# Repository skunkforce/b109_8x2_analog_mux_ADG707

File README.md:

# edgy_board number b109
This design is part of the [edgy board project](https://github.com/skunkforce/edgy_boards). It provides the functionality of chip ADG707 an 8x2 analog mux. 

# getting started
This repository uses submodules. After cloning use the command 

```$ git submodule update --init --recursive```

to pull the submodules before opening the project with kicad. 

# Tests
Tests can be found in [TESTS.md](TESTS.md)

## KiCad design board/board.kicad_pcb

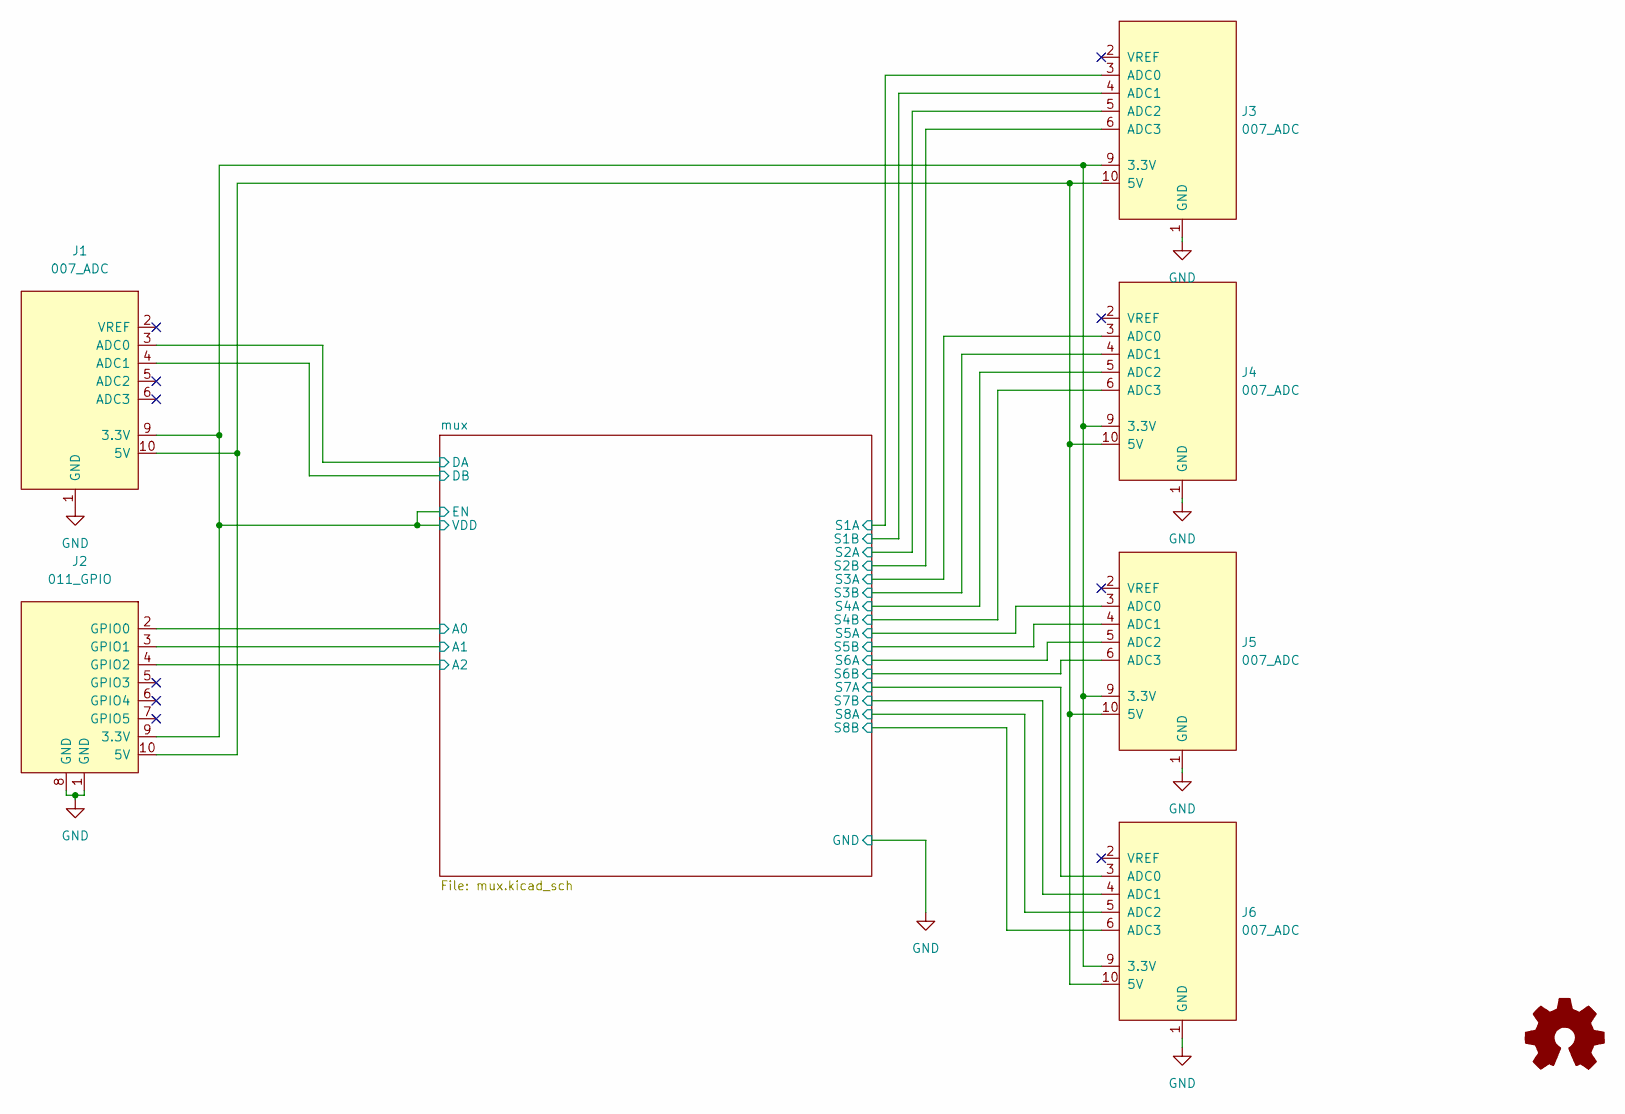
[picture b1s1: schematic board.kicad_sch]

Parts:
J1: 007_ADC; on_edge_2x05_device; lcsc C14663
J2: 011_GPIO; on_edge_2x05_device
J3, J4, J5, J6: 007_ADC; on_edge_2x05_host
LOGO1: Logo_Open_Hardware_Small; OSHW-Symbol_6.7x6mm_SilkScreen

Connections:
/mux/A0: J2.2 (GPIO0); also elsewhere on the board
/mux/A1: J2.3 (GPIO1); also elsewhere on the board
/mux/A2: J2.4 (GPIO2); also elsewhere on the board
/mux/DA: J1.3 (ADC0); also elsewhere on the board
/mux/DB: J1.4 (ADC1); also elsewhere on the board
/mux/EN: J1.9 (3.3V), J2.9 (3.3V), J3.9 (3.3V), J4.9 (3.3V), J5.9 (3.3V), J6.9 (3.3V); also elsewhere on the board
/mux/S1A: J3.3 (ADC0); also elsewhere on the board
/mux/S1B: J3.4 (ADC1); also elsewhere on the board
/mux/S2A: J3.5 (ADC2); also elsewhere on the board
/mux/S2B: J3.6 (ADC3); also elsewhere on the board
/mux/S3A: J4.3 (ADC0); also elsewhere on the board
/mux/S3B: J4.4 (ADC1); also elsewhere on the board
/mux/S4A: J4.5 (ADC2); also elsewhere on the board
/mux/S4B: J4.6 (ADC3); also elsewhere on the board
/mux/S5A: J5.3 (ADC0); also elsewhere on the board
/mux/S5B: J5.4 (ADC1); also elsewhere on the board
/mux/S6A: J5.5 (ADC2); also elsewhere on the board
/mux/S6B: J5.6 (ADC3); also elsewhere on the board
/mux/S7A: J6.3 (ADC0); also elsewhere on the board
/mux/S7B: J6.4 (ADC1); also elsewhere on the board
/mux/S8A: J6.5 (ADC2); also elsewhere on the board
/mux/S8B: J6.6 (ADC3); also elsewhere on the board
GND: J1.1 (GND), J2.1 (GND), J2.8 (GND), J3.1 (GND), J4.1 (GND), J5.1 (GND), J6.1 (GND); also elsewhere on the board
unnamed: J1.10 (5V), J2.10 (5V), J3.10 (5V), J4.10 (5V), J5.10 (5V), J6.10 (5V)

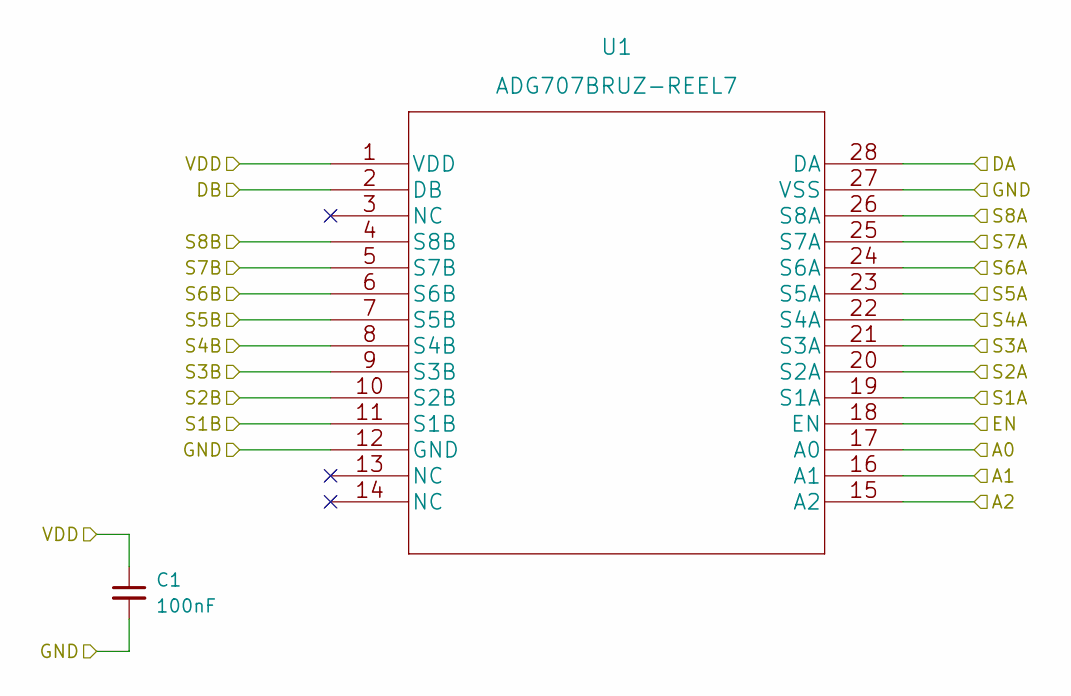
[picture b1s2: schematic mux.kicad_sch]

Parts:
C1: 100nF; C_0603_1608Metric
U1: ADG707BRUZ-REEL7; lcsc C246080

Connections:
/mux/A0: U1.17 (A0); also elsewhere on the board
/mux/A1: U1.16 (A1); also elsewhere on the board
/mux/A2: U1.15 (A2); also elsewhere on the board
/mux/DA: U1.28 (DA); also elsewhere on the board
/mux/DB: U1.2 (DB); also elsewhere on the board
/mux/EN: C1.1, U1.1 (VDD), U1.18 (EN); also elsewhere on the board
/mux/S1A: U1.19 (S1A); also elsewhere on the board
/mux/S1B: U1.11 (S1B); also elsewhere on the board
/mux/S2A: U1.20 (S2A); also elsewhere on the board
/mux/S2B: U1.10 (S2B); also elsewhere on the board
/mux/S3A: U1.21 (S3A); also elsewhere on the board
/mux/S3B: U1.9 (S3B); also elsewhere on the board
/mux/S4A: U1.22 (S4A); also elsewhere on the board
/mux/S4B: U1.8 (S4B); also elsewhere on the board
/mux/S5A: U1.23 (S5A); also elsewhere on the board
/mux/S5B: U1.7 (S5B); also elsewhere on the board
/mux/S6A: U1.24 (S6A); also elsewhere on the board
/mux/S6B: U1.6 (S6B); also elsewhere on the board
/mux/S7A: U1.25 (S7A); also elsewhere on the board
/mux/S7B: U1.5 (S7B); also elsewhere on the board
/mux/S8A: U1.26 (S8A); also elsewhere on the board
/mux/S8B: U1.4 (S8B); also elsewhere on the board
GND: C1.2, U1.12 (GND), U1.27 (VSS); also elsewhere on the board

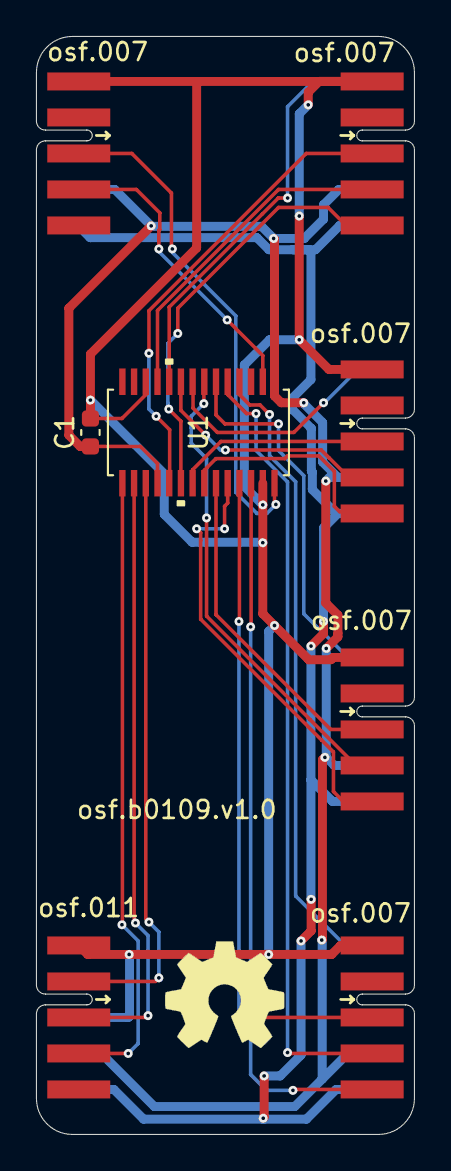
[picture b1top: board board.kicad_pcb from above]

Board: 2 copper layers, 21.0 x 61.0 mm, 9 parts (0 on the bottom side), 24 nets.

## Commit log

2023-03-13 initial
2024-02-05 added lcsc part numbers
